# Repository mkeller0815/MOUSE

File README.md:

# MOUSE

MOUSE (Mario's Own Unique SingleBoard Engine) is minimal 8bit computer system based on the W65C02 microprocessor.

## Files

 * Documentation - documentation, datasheets, images etc.
 * LICENSE - filed under MIT license
 * PCB - KiCad files for pcb of the computer
 * README.md - this file
 * Source - all the sources for the I/O system, minimal OS and some software

Each subdirectory has its own README file with further information about the content

## Concept

This is a single board computer with a minimal chipcount. It is powerd by a USB2Serial Aadapter that also provides 
access to the computer via serial connection. Any TTL serial-adapter that has RX/TX lines as well as +5V and GND 
is suitable.

The computer has 32k SRAM and 8k ROM. There are also 2 extension headers for additional hardware

## Hardware

 * W65C02 CPU 
 * 32k SRAM
 * 8k EEPROM
 * M6850 ACIA (serial interface)
 * DS1813 reset circuit

## Software 

 * DRIVER - provideing highlevel access to peripherals
 * MIOS - Minimal Input/Output System 
 * M-OS - MOUSE OS 
 * Programms - third party software adapted to MOUSE

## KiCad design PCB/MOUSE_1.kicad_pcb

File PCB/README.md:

# MOUSE - PCB

This is the pcb sectoion of the project. It provides the schematic as well as the pcb layout and all the files that are needed to create or order a pcb.

## IMPORTANT NOTE

Currently this part is under development and will change in the near future. 

There are two known problems at the moment that make the expension ports less usefull. In the address decoding there are two lines swapped.

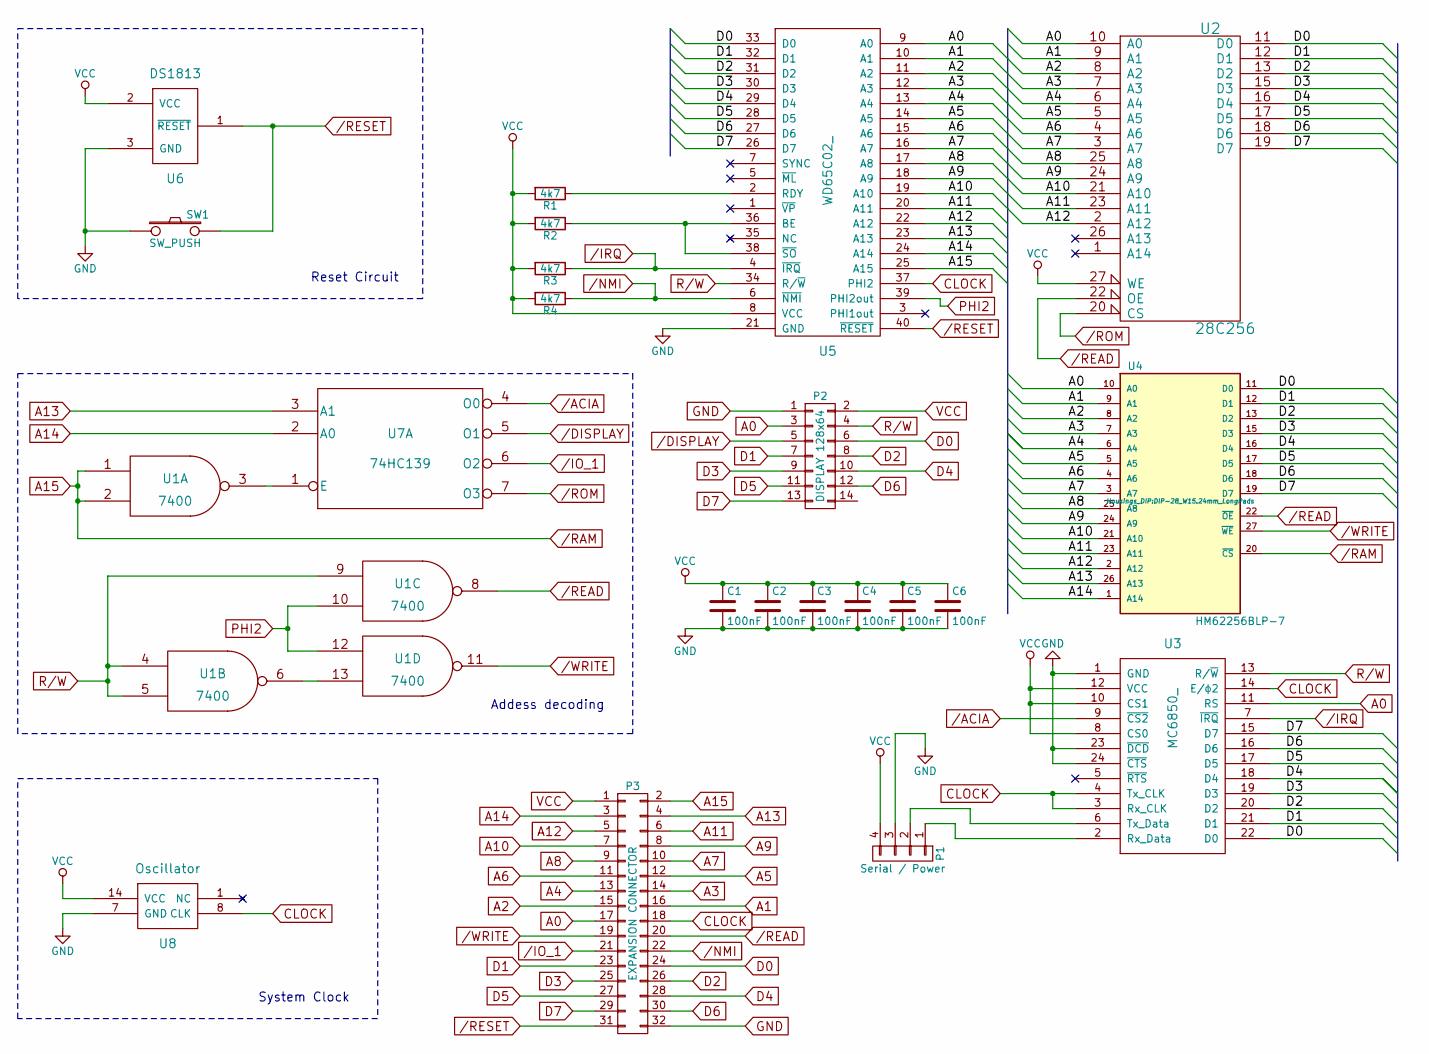
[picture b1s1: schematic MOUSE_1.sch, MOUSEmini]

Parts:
C1, C2, C3, C4, C5, C6: 100nF; C_Disc_D3_P2.5
P1: Serial / Power; Pin_Header_Straight_1x04
P2: DISPLAY 128x64; Pin_Header_Straight_2x07
P3: EXPANSION CONNECTOR; Pin_Header_Straight_2x16
R1, R2, R3, R4: 4k7; Resistor_Horizontal_RM10mm
SW1: SW_PUSH; SW_PUSH_SMALL
U1: 7400; DIP-14_W7.62mm_LongPads
U2: 28C256; DIP-28_W15.24mm_LongPads
U3: MC6850_; DIP-24_W15.24mm_LongPads
U4: HM62256BLP-7; DIP-28_W15.24mm_LongPads
U5: WD65C02_; DIP-40_W15.24mm_LongPads
U6: DS1813; TO-92_Inline_Narrow_Oval
U7: 74HC139; DIP-16_W7.62mm_LongPads
U8: Oscillator; DIP-14_W7.62mm_LongPads

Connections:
/ACIA: U3.9 (~CS2), U7.4 (O0)
/DISPLAY: P2.5, U7.5 (O1)
/IO_1: P3.21, U7.6 (O2)
/IRQ: R3.1, U3.7 (~IRQ), U5.4 (~IRQ)
/NMI: P3.22, R4.1, U5.6 (~NMI)
/READ: P3.20, U1.8, U2.22 (OE), U4.22 (~OE)
/RESET: P3.31, SW1.2, U5.40 (~RESET), U6.1 (~RESET)
/ROM: U2.20 (CS), U7.7 (O3)
/WRITE: P3.19, U1.11, U4.27 (~WE)
A0: P2.3, P3.17, U2.10 (A0), U3.11 (RS), U4.10 (A0), U5.9 (A0)
A1: P3.16, U2.9 (A1), U4.9 (A1), U5.10 (A1)
A2: P3.15, U2.8 (A2), U4.8 (A2), U5.11 (A2)
A3: P3.14, U2.7 (A3), U4.7 (A3), U5.12 (A3)
A4: P3.13, U2.6 (A4), U4.6 (A4), U5.13 (A4)
A5: P3.12, U2.5 (A5), U4.5 (A5), U5.14 (A5)
A6: P3.11, U2.4 (A6), U4.4 (A6), U5.15 (A6)
A7: P3.10, U2.3 (A7), U4.3 (A7), U5.16 (A7)
A8: P3.9, U2.25 (A8), U4.25 (A8), U5.17 (A8)
A9: P3.8, U2.24 (A9), U4.24 (A9), U5.18 (A9)
A10: P3.7, U2.21 (A10), U4.21 (A10), U5.19 (A10)
A11: P3.6, U2.23 (A11), U4.23 (A11), U5.20 (A11)
A12: P3.5, U2.2 (A12), U4.2 (A12), U5.22 (A12)
A13: P3.4, U4.26 (A13), U5.23 (A13), U7.3 (A1)
A14: P3.3, U4.1 (A14), U5.24 (A14), U7.2 (A0)
A15: P3.2, U1.1, U1.2, U4.20 (~CS), U5.25 (A15)
CLOCK: P3.18, U3.3 (Rx_CLK), U3.4 (Tx_CLK), U3.14 (E/ϕ2), U5.37 (PHI2), U8.8 (CLK)
D0: P2.6, P3.24, U2.11 (D0), U3.22 (D0), U4.11 (D0), U5.33 (D0)
D1: P2.7, P3.23, U2.12 (D1), U3.21 (D1), U4.12 (D1), U5.32 (D1)
D2: P2.8, P3.26, U2.13 (D2), U3.20 (D2), U4.13 (D2), U5.31 (D2)
D3: P2.9, P3.25, U2.15 (D3), U3.19 (D3), U4.15 (D3), U5.30 (D3)
D4: P2.10, P3.28, U2.16 (D4), U3.18 (D4), U4.16 (D4), U5.29 (D4)
D5: P2.11, P3.27, U2.17 (D5), U3.17 (D5), U4.17 (D5), U5.28 (D5)
D6: P2.12, P3.30, U2.18 (D6), U3.16 (D6), U4.18 (D6), U5.27 (D6)
D7: P2.13, P3.29, U2.19 (D7), U3.15 (D7), U4.19 (D7), U5.26 (D7)
GND: C1.2, C2.2, C3.2, C4.2, C5.2, C6.2, P1.3, P2.1, P3.32, SW1.1, U1.7 (GND), U2.14 (GND), U3.1 (GND), U3.23 (~DCD), U3.24 (~CTS), U4.14 (GND), U5.21 (GND), U6.3 (GND), U7.8 (GND), U8.7 (GND)
unnamed: P1.1, U3.2 (Rx_Data)
unnamed: P1.2, U3.6 (Tx_Data)
unnamed: R1.1, U5.2 (RDY)
unnamed: R2.1, U5.36 (BE), U5.38 (~SO)
unnamed: U1.3, U7.1 (E)
unnamed: U1.6, U1.13
PHI2: U1.10, U1.12, U5.39 (PHI2out)
R/W: P2.4, U1.4, U1.5, U1.9, U3.13 (R/~W), U5.34 (R/~W)
VCC: C1.1, C2.1, C3.1, C4.1, C5.1, C6.1, P1.4, P2.2, P3.1, R1.2, R2.2, R3.2, R4.2, U1.14 (VCC), U2.27 (WE), U2.28 (VCC), U3.8 (CS0), U3.10 (CS1), U3.12 (VCC), U4.28 (VCC), U5.8 (VCC), U6.2 (VCC), U7.16 (VCC), U8.14 (VCC)

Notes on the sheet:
Reset Circuit
Addess decoding
System Clock

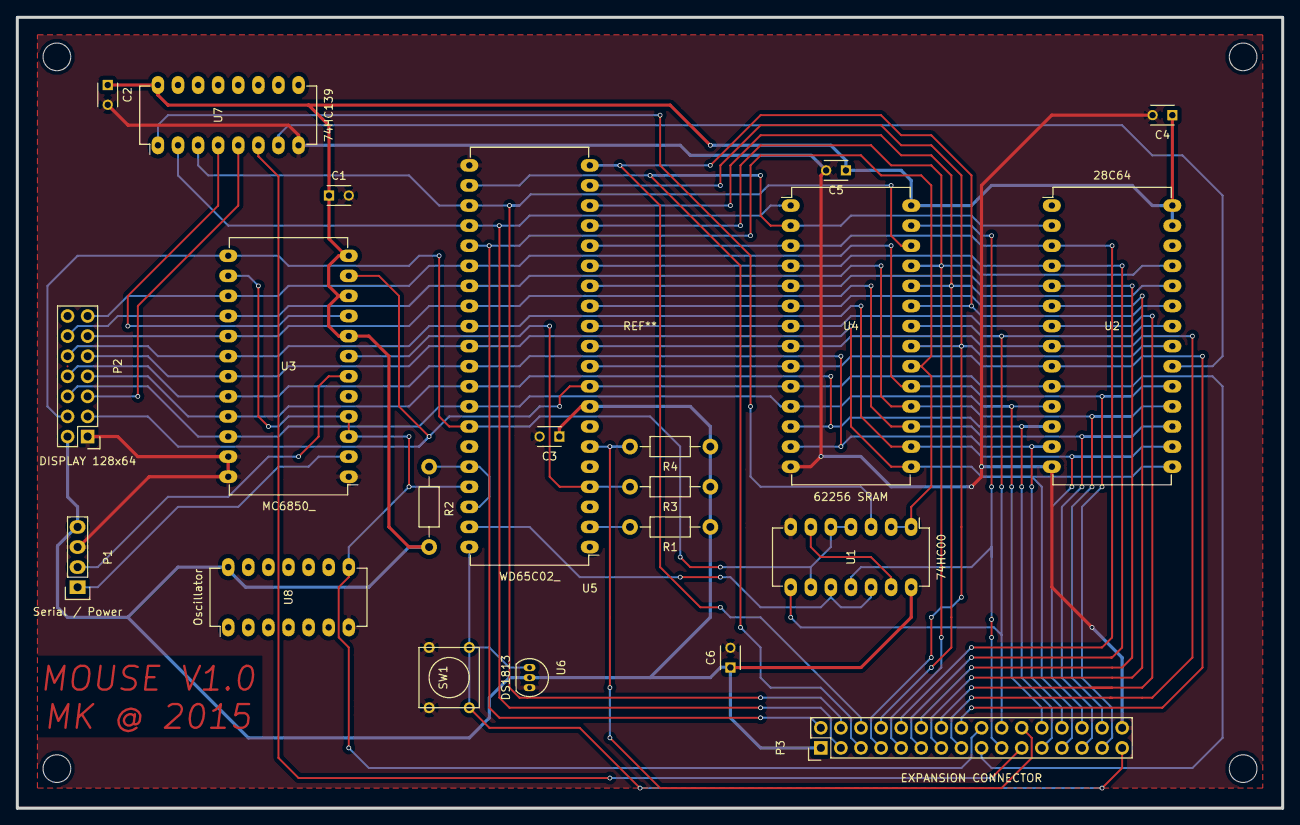
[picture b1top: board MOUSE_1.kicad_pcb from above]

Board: 2 copper layers, 160.0 x 100.0 mm, 22 parts (0 on the bottom side), 44 nets.

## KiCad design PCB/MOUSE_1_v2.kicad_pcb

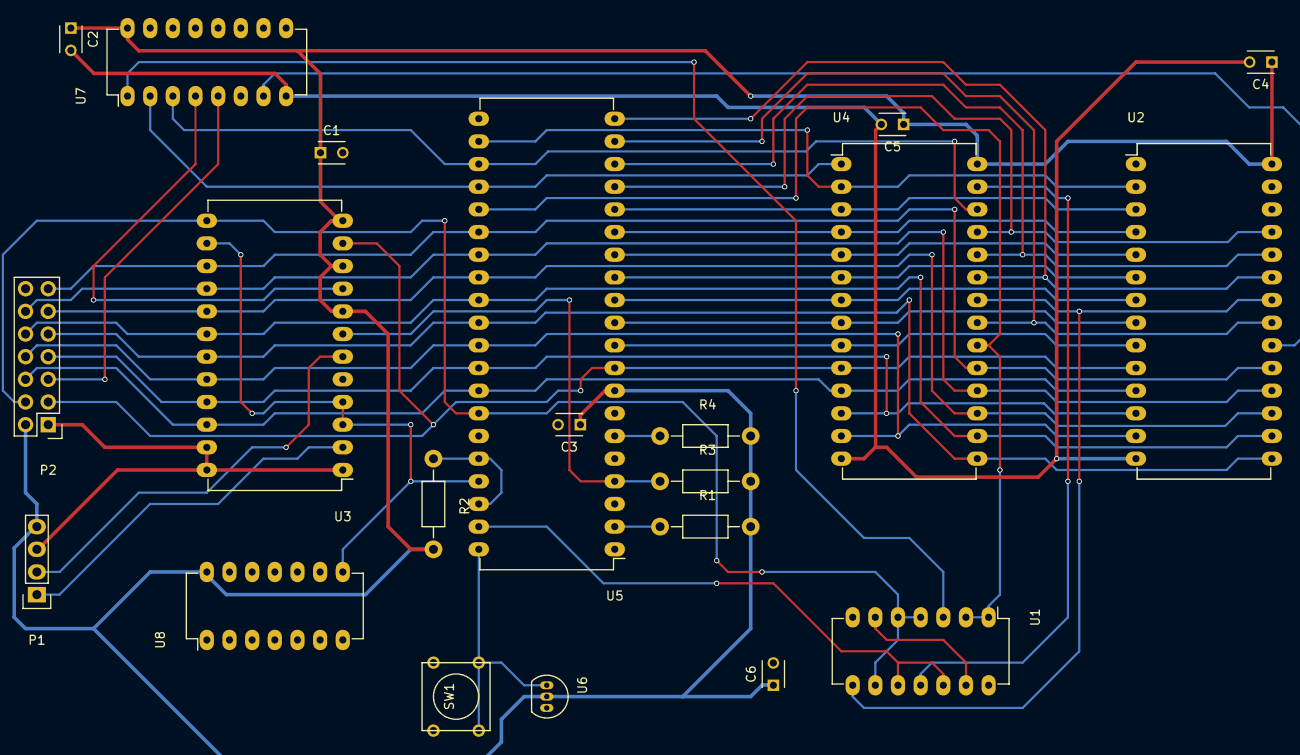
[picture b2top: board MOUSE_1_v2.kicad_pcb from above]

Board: 2 copper layers, 21 parts (0 on the bottom side), 43 nets.

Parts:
C1, C2, C3, C4, C5, C6: 100nF; C_Disc_D3_P2.5
P1: Serial / Power; Pin_Header_Straight_1x04
P2: DISPLAY 128x64; Pin_Header_Straight_2x07
R1, R2, R3, R4: 4k7; Resistor_Horizontal_RM10mm
SW1: SW_PUSH; SW_PUSH_SMALL
U1: 7400; DIP-14_W7.62mm_LongPads
U2: 28C256; DIP-28_W15.24mm_LongPads
U3: MC6850_; DIP-24_W15.24mm_LongPads
U4: HM62256BLP-7; DIP-28_W15.24mm_LongPads
U5: WD65C02_; DIP-40_W15.24mm_LongPads
U6: DS1813; TO-92_Inline_Narrow_Oval
U7: 74HC139; DIP-16_W7.62mm_LongPads
U8: Oscillator; DIP-14_W7.62mm_LongPads

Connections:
/A1: U2.9, U4.9, U5.10
/A2: U2.8, U4.8, U5.11
/A3: U2.7, U4.7, U5.12
/A4: U2.6, U4.6, U5.13
/A5: U2.5, U4.5, U5.14
/A6: U2.4, U4.4, U5.15
/A7: U2.3, U4.3, U5.16
/A8: U2.25, U4.25, U5.17
/A9: U2.24, U4.24, U5.18
/A10: U2.21, U4.21, U5.19
/A11: U2.23, U4.23, U5.20
/A12: U2.2, U4.2, U5.22
/ACIA: U3.9, U7.4
/DISPLAY: P2.5, U7.5
/IRQ: R3.1, U3.7, U5.4
/NMI: R4.1, U5.6
/RAM: U1.1, U1.2, U4.20, U5.25
/READ: U1.8, U2.22, U4.22
/RESET: SW1.2, U5.40, U6.1
/ROM: U2.20, U7.7
/WRITE: U1.11, U4.27
A0: P2.3, U2.10, U3.11, U4.10, U5.9
A13: U4.26, U5.23, U7.3
A14: U4.1, U5.24, U7.2
CLOCK: U3.3, U3.4, U3.14, U5.37, U8.8
D0: P2.6, U2.11, U3.22, U4.11, U5.33
D1: P2.7, U2.12, U3.21, U4.12, U5.32
D2: P2.8, U2.13, U3.20, U4.13, U5.31
D3: P2.9, U2.15, U3.19, U4.15, U5.30
D4: P2.10, U2.16, U3.18, U4.16, U5.29
D5: P2.11, U2.17, U3.17, U4.17, U5.28
D6: P2.12, U2.18, U3.16, U4.18, U5.27
D7: P2.13, U2.19, U3.15, U4.19, U5.26
GND: C1.2, C2.2, C3.2, C4.2, C5.2, C6.2, P1.3, P2.1, SW1.1, U1.7, U2.14, U3.1, U3.23, U3.24, U4.14, U5.21, U6.3, U7.8, U8.7
unnamed: P1.1, U3.2
unnamed: P1.2, U3.6
unnamed: R1.1, U5.2
unnamed: R2.1, U5.36, U5.38
unnamed: U1.3, U7.1
unnamed: U1.6, U1.13
PHI2: U1.10, U1.12, U5.39
R/W: P2.4, U1.4, U1.5, U1.9, U3.13, U5.34
VCC: C1.1, C2.1, C3.1, C4.1, C5.1, C6.1, P1.4, P2.2, R1.2, R2.2, R3.2, R4.2, U1.14, U2.27, U2.28, U3.8, U3.10, U3.12, U4.28, U5.8, U6.2, U7.16, U8.14

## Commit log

2015-10-14 initial project version
2015-10-14 Doc README extended
2018-02-26 no real change
